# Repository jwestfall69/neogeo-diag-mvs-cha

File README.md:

# neogeo-diag-mvs-cha

## Overview
This is a custom NeoGeo MVS CHA board that is used in conjunction with the [NeoGeo Diag Bios](https://github.com/jwestfall69/neogeo-diag-bios) that allows for testing the Z80 sound system with a custom diag M1 rom.  This doesn't allow for any new type of testing that was done previously, but make it possible to create a diag CHA board without having to sacrifice a original SNK CHA board.

The NeoGeo uses bank switching to allow full access to the M1 rom.  This is normally handled by a custom NEO-ZMC chip on the CHA board.  I ended up making 3 different boards you can choose from to deal with this bank switching:

A Board that uses a original NEO-ZMC:
<br>

2 Boards that replace the NEO-ZMC with a CPLD (Socketed PLCC44 and TQFP44):

Personally I would go with the NEO-ZMC based board since the NEO-ZMC is available as NOS for around $2 each.  More on this in the BOM below.  Additionally with the chip shortage its a little difficult to get the CPLDs, plus the fun of programming them.

## PCB Manufacturing
PCB should be 1.6mm thickness.  With these boards likely being inserted and removed numerous times its suggested you use ENIG surface finishing and gold fingers w/chamfering.

I've been using [jlcpcb](https://jlcpcb.com/) for PCB manufacturing.  Just watch out that by default they will add an order number to the silk screen unless you tell them not to.

## BOMs
**IMPORTANT:**

  * The 32 pin DIP sockets listed in the BOMs are special low profile ones.  Normal sockets + EPROM are to tall for the board to be able to fit behind the PROG board.
  * Stock of the CPLD is pretty low everywhere.  If you can't find them on digikey/mouser, you might be able to buy them directly from [Microchip](https://www.microchipdirect.com/).
  * If you buy a used CPLD its possible the JTAG pins were repurposed as I/O pins.  This will make it impossible to re-program with JTAG.
  * When buying the EPROMs I would advise against buying any that claimed to be new.  Sellers claiming this maybe trying to sell 
  slower speed variants re-labeled as something faster or just straight up fakes.

### NEO-ZMC based board
| Quantity | Description | Part Number | Digikey | Notes |
|:--------:|:------------|-------------|---------|-------|
| 1        | NEO-ZMC | NEO-ZMC | | NOS Availible:<br> - On [Aliexpress](https://www.aliexpress.us/item/2251832763681253.html?gatewayAdapt=glo2usa4itemAdapt)<br>- On [arcade-projects.com](https://www.arcade-projects.com/threads/openkeys-neogeo-diag-prog-boards.24392/) |
| 2        | 74HC574 pin 14 SOIC | SN74HC574NSR | [296-31816-1-ND](https://www.digikey.com/en/products/detail/texas-instruments/SN74HC574NSR/1571235) | |
| 2       | Low Profile 32pin DIP Socket | 115-93-632-41-003000 | [ED5632-ND](https://www.digikey.com/en/products/detail/mill-max-manufacturing-corp/115-93-632-41-003000/81902) | This is optional if you want just solder the eproms to the board |
| 2       | 1Mbit (128k x 8bit) 32 pin EPROM, 150ns or faster | 27C1001<br>or<br>27C010 | | |
| 5        | 100nf / 0.1uf Ceramic Capacitor 0805 Size | CL21B104KBCNNNC | [1276-1003-2-ND](https://www.digikey.com/en/products/detail/samsung-electro-mechanics/CL21B104KBCNNNC/3886661) | Any 100nf 0805 is fine |

### CPLD PLCC44 (Socket) based board
| Quantity | Description | Part Number | Digikey | Notes |
|:--------:|:------------|-------------|---------|-------|
| 1        | CLPD PLCC 44 pin | Microchip/Atmel ATF1502AS-xxJU44<br>or<br>ATF1504AS-xxJU44 | [ATF1502AS-7JX44-ND](https://www.digikey.com/en/products/detail/microchip-technology/ATF1502AS-7JX44/1027048)<br>[ATF1504AS-10JU44](https://www.digikey.com/en/products/detail/microchip-technology/ATF1504AS-10JU44/1118923) | Other speeds should work too |
| 1        | PLCC 44 pin through hole socket | | | |
| 2        | 74HC574 pin 14 SOIC | SN74HC574NSR | [296-31816-1-ND](https://www.digikey.com/en/products/detail/texas-instruments/SN74HC574NSR/1571235) | |
| 2       | Low Profile 32pin DIP Socket | 115-93-632-41-003000 | [ED5632-ND](https://www.digikey.com/en/products/detail/mill-max-manufacturing-corp/115-93-632-41-003000/81902) | This is optional if you want just solder the eproms to the board |
| 2       | 1Mbit (128k x 8bit) 32 pin EPROM, 150ns or faster | 27C1001<br>or<br>27C010 | | |
| 8       | 100nf / 0.1uf Ceramic Capacitor 0805 Size | CL21B104KBCNNNC | [1276-1003-2-ND](https://www.digikey.com/en/products/detail/samsung-electro-mechanics/CL21B104KBCNNNC/3886661) | Any 100nf 0805 is fine |

### CPLD TQFP44 based board
| Quantity | Description | Part Number | Digikey | Notes |
|:--------:|:------------|-------------|---------|-------|
| 1        | CLPD TQFP 44 pin | Microchip/Atmel ATF1502AS-xxAU44<br>or<br>ATF1504AS-xxAU44 | [ATF1502AS-10AU44](https://www.digikey.com/en/products/detail/microchip-technology/ATF1502AS-10AU44/1008375)<br>[ATF1504AS-10AU44](https://www.digikey.com/en/products/detail/microchip-technology/ATF1504AS-10AU44/1008359) | Other speeds should work too |
| 2        | 74HC574 pin 14 SOIC | SN74HC574NSR | [296-31816-1-ND](https://www.digikey.com/en/products/detail/texas-instruments/SN74HC574NSR/1571235) | |
| 2       | Low Profile 32pin DIP Socket | 115-93-632-41-003000 | [ED5632-ND](https://www.digikey.com/en/products/detail/mill-max-manufacturing-corp/115-93-632-41-003000/81902) | This is optional if you want just solder the eproms to the board |
| 2       | 1Mbit (128k x 8bit) 32 pin EPROM, 150ns or faster | 27C1001<br>or<br>27C010 | | |
| 8       | 100nf / 0.1uf Ceramic Capacitor 0805 Size | CL21B104KBCNNNC | [1276-1003-2-ND](https://www.digikey.com/en/products/detail/samsung-electro-mechanics/CL21B104KBCNNNC/3886661) | Any 100nf 0805 is fine |

## Assembly
  * Reminder from above that normal 32 pin DIP sockets will be to tall
  * On the NEO-ZMC board, take note of pin 1 location of the NEO-ZMC chip as its rotated 180 degrees from what you might expect.

## Programming the CPLD

Both CPLD based boards have a JTAG port on left side that can be used for programming the CPLD.  I've been using this [FT232H](https://www.amazon.com/dp/B07T9CPMHT?psc=1&ref=ppx_yo2ov_dt_b_product_details) based programmer along with [openocd](https://openocd.org/) software to program the CPLD.

Here is a picture of the programmer and the cable I made for it:

The programmer has pin labels on the bottom of the board.

| Programmer PIN | J-TAG PIN |
|:--------------:|:---------:|
| AD0            | TCK       |
| AD1            | TDI       |
| AD2            | TDO       |
| AD3            | TMS       |
| GND            | GND       |
| +5V            | VCC       |

I haven't done JTAG stuff before, but believe this programmer not normal in that its supplying 5V to power the CPLD, whereas I think most JTAG programmers rely on something else to supply power to the CPLD and the VCC/GND pins are just used for VCC/GND reference.

Since this programmer is supplying power, it would be powering the entire CHA board including to the EPROMS/74HC574 chips.  I haven't run into any USB over current issues doing this.  Obviously don't plug in the programmer into the CHA board if its also plugged into an MVS motherboard.

Its not necessary to solder the JTAG cable to the JTAG port on the CHA board, just insert the pins into the through hole and hold it an angle so the pins are touching the sides of the through holes like this:

As noted above I've been using openocd software for programming.  I've only used it on linux and it should be an existing package your distro.  For the following openocd commands below the location of the um232h.cfg maybe different depending on where your distro installs interface config files.  Additionally if you use a different programmer you might need to use a completely different interface config.

**Make sure the CPLD is detected**
```
# openocd -f /usr/share/openocd/scripts/interface/ftdi/um232h.cfg -c "adapter speed 400" -c "transport select jtag" -c init -c scan_chain -c shutdown

Open On-Chip Debugger 0.11.0+dev-snapshot (2023-02-14-01:09)
Licensed under GNU GPL v2
For bug reports, read
        http://openocd.org/doc/doxygen/bugs.html
adapter speed: 400 kHz

jtag
Info : clock speed 400 kHz
Warn : There are no enabled taps.  AUTO PROBING MIGHT NOT WORK!!
Info : JTAG tap: auto0.tap tap/device found: 0x0150403f (mfg: 0x01f (Atmel), part: 0x1504, ver: 0x0)
Warn : AUTO auto0.tap - use "jtag newtap auto0 tap -irlen 3 -expected-id 0x0150403f"
Warn : gdb services need one or more targets defined
   TapName             Enabled  IdCode     Expected   IrLen IrCap IrMask
-- ------------------- -------- ---------- ---------- ----- ----- ------
 0 auto0.tap              Y     0x0150403f 0x00000000     3 0x01  0x03

shutdown command invoked

```
You want to see an IdCode of 0x01504xxx or 0x01502xxx based on which CPLD you are using.

**Programming the CPLD**<br>
For programming you will need the .svf firmware file for the CPLD you are using.  In the below example I have a ATF1504AS-7AX44 TQFP CPLD, so I use the atf1504as-tqfp44.svf firmware.

```
# openocd -f /usr/share/openocd/scripts/interface/ftdi/um232h.cfg -c "adapter speed 400" -c "transport select jtag" -c init -c "svf atf1504as-tqfp44/atf1504as-tqfp44.svf" -c shutdown

Open On-Chip Debugger 0.11.0+dev-snapshot (2023-02-14-01:09)
Licensed under GNU GPL v2
For bug reports, read
        http://openocd.org/doc/doxygen/bugs.html
adapter speed: 400 kHz

jtag
Info : clock speed 400 kHz
Warn : There are no enabled taps.  AUTO PROBING MIGHT NOT WORK!!
Info : JTAG tap: auto0.tap tap/device found: 0x0150403f (mfg: 0x01f (Atmel), part: 0x1504, ver: 0x0)
Warn : AUTO auto0.tap - use "jtag newtap auto0 tap -irlen 3 -expected-id 0x0150403f"
Warn : gdb services need one or more targets defined
svf processing file: "atf1504as-tqfp44/atf1504as-tqfp44.svf"
TRST ABSENT;
ENDIR IDLE;
ENDDR IDLE;
HDR 0;
HIR 0;
TDR 0;
TIR 0;
RUNTEST 50021E-6 SEC;
STATE RESET;
STATE IDLE;
RUNTEST 50021E-6 SEC;
SIR 10 TDI (280);
SDR 10 TDI (1b9);
STATE IDLE;
SIR 10 TDI (059);
        MASK (ffffffff);
STATE IDLE;
SIR 10 TDI (2b3);
SIR 10 TDI (29e);

...

SIR 10 TDI (293);
        MASK (ffff);
STATE IDLE;
SIR 10 TDI (2a1);
SDR 11 TDI (100);
SIR 10 TDI (28c);
STATE IDLE;
RUNTEST 20001E-6 SEC;
SIR 10 TDI (291);
        MASK (ffffffff);
STATE IDLE;
SIR 10 TDI (280);
SDR 10 TDI (000);
STATE IDLE;
RUNTEST 10001E-6 SEC;
STATE RESET;
RUNTEST 50021E-6 SEC;

Time used: 0m12s393ms
svf file programmed successfully for 3299 commands with 0 errors

shutdown command invoked

```

## Programming the EPROMs
The M1 EPROM should be programmed using the diag M1 ROM provided with the neogeo diag bios.

The S1 EPROM can be programmed with most any S1 ROM from any game.  I usually just use 201-s1.s1 from mslug mame romset.

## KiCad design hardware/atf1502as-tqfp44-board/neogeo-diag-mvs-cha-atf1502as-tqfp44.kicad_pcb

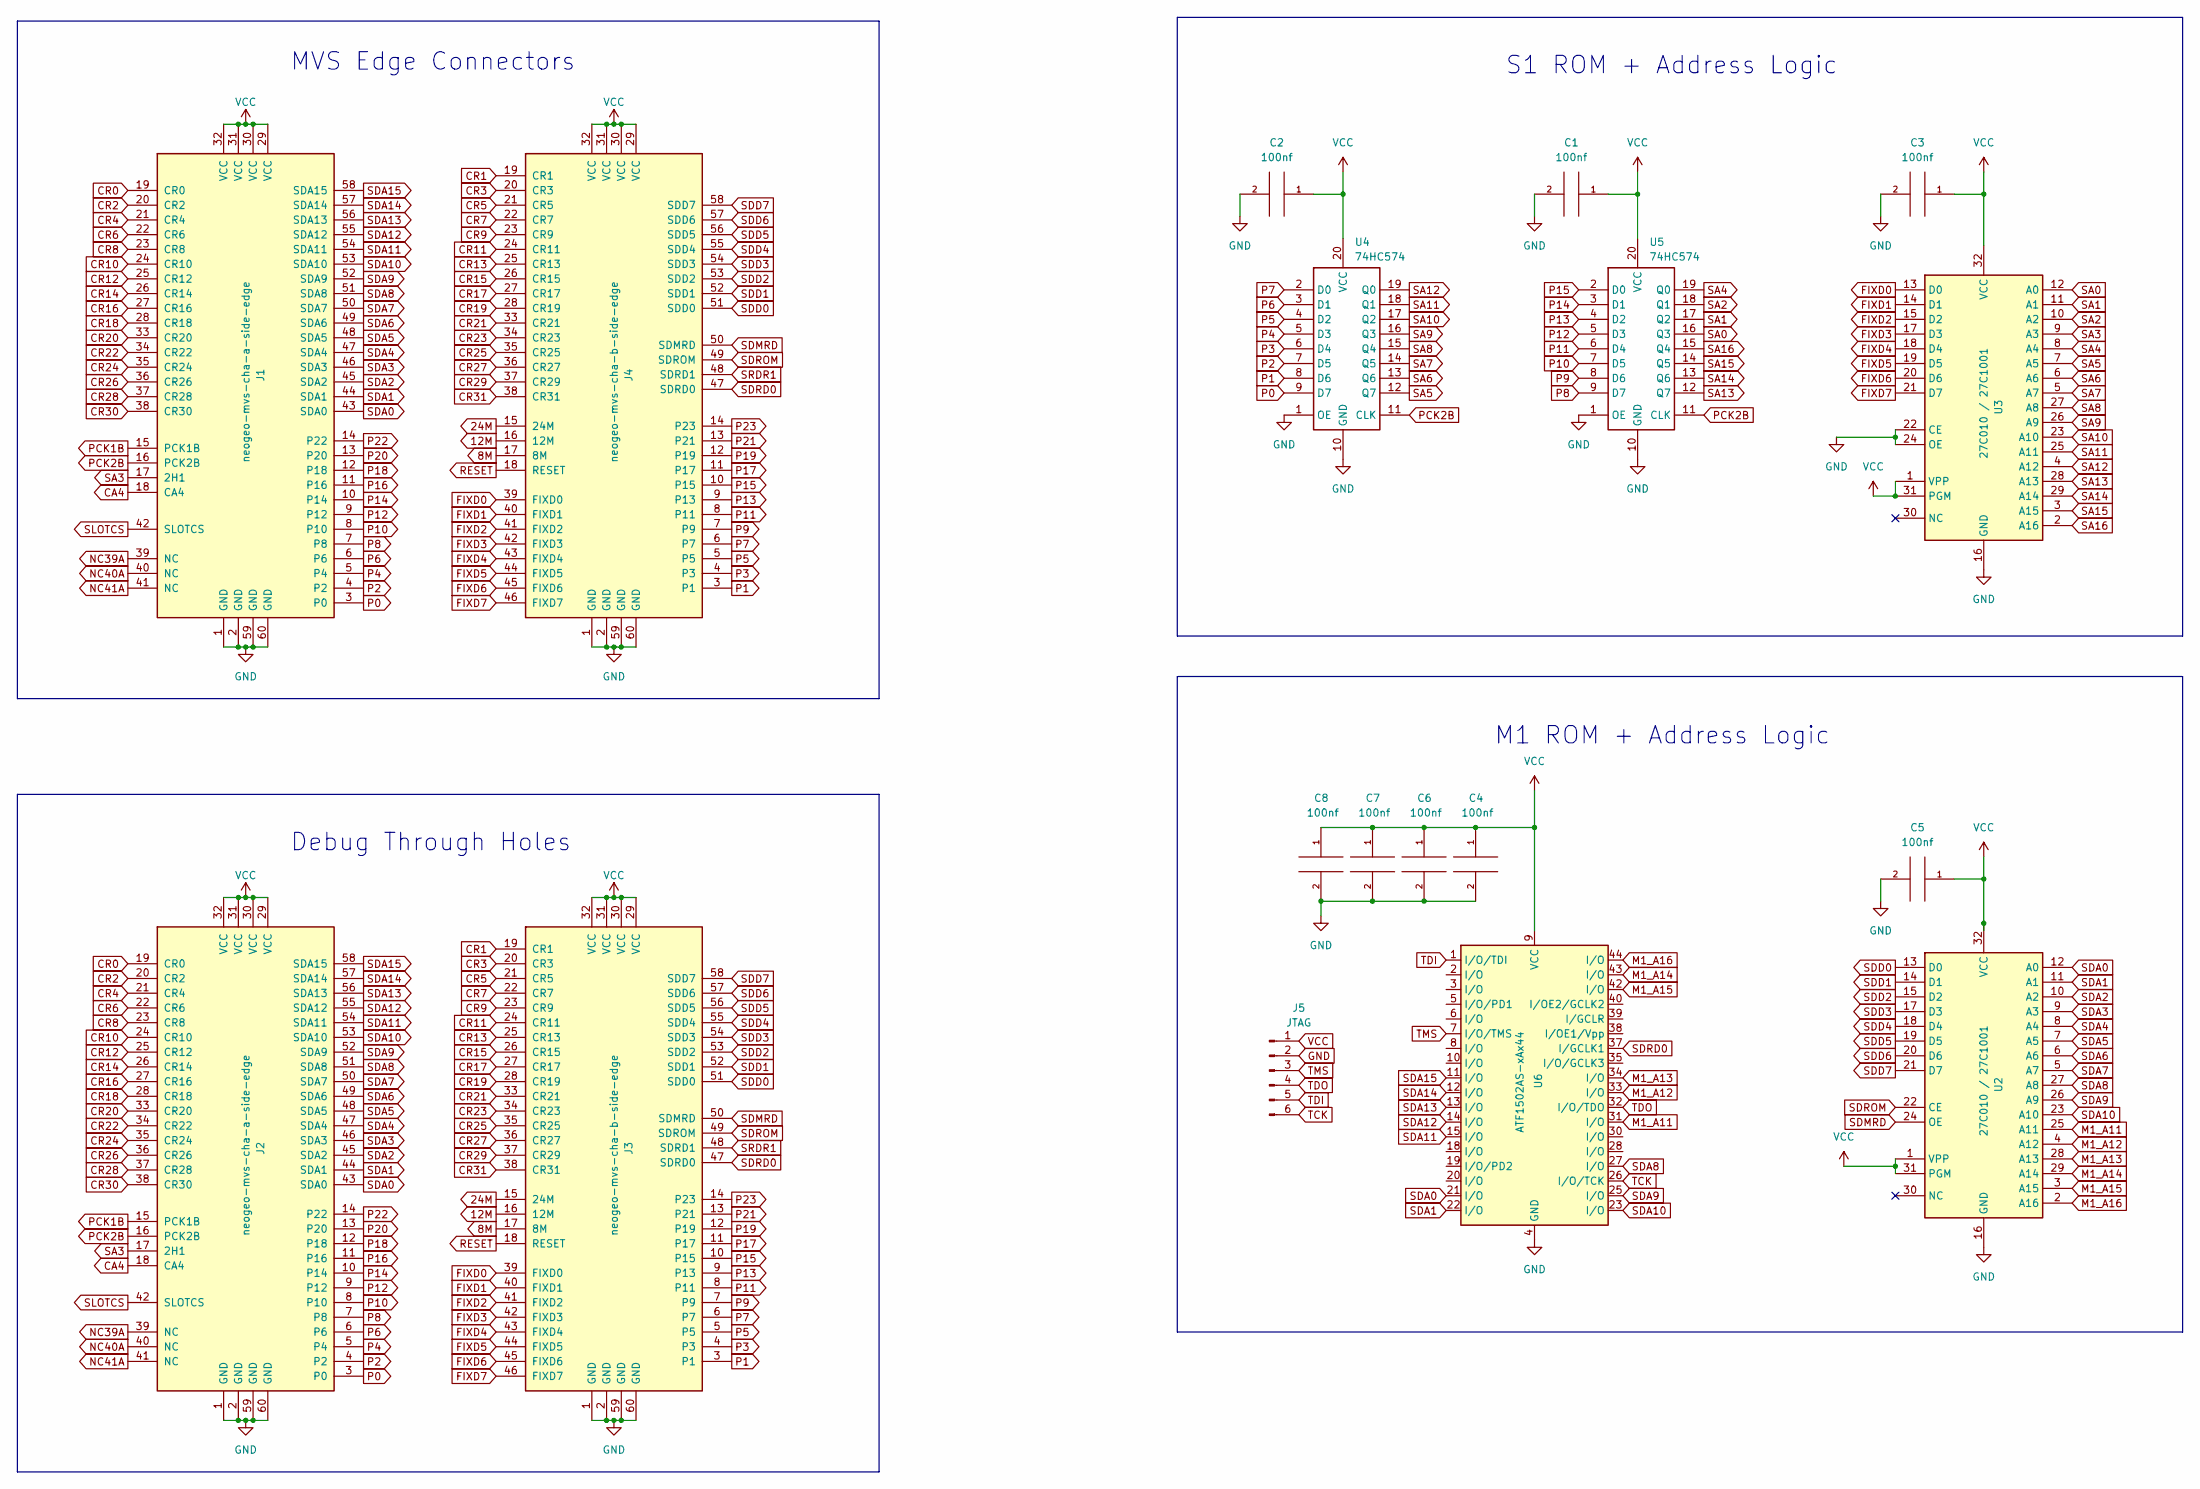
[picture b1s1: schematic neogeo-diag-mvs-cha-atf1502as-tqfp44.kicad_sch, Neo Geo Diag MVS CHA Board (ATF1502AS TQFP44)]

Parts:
C1, C2, C3, C4, C5, C6, C7, C8: 100nf; C_0805_2012Metric
J1: neogeo-mvs-cha-a-side-edge; neogeo-mvs-a-side-edge
J2: neogeo-mvs-cha-a-side-edge; neogeo-mvs-cha-edge-test-points
J3: neogeo-mvs-cha-b-side-edge; neogeo-mvs-cha-edge-test-points
J4: neogeo-mvs-cha-b-side-edge; neogeo-mvs-b-side-edge
J5: JTAG; PinHeader_1x06_P2.54mm_Vertical
U2, U3: 27C010 / 27C1001; DIP-32_W15.24mm_Socket_LongPads
U4, U5: 74HC574; SO-20_5.3x12.6mm_P1.27mm
U6: ATF1502AS-xAx44; TQFP-44_10x10mm_P0.8mm

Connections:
8M: J3.17 (8M), J4.17 (8M)
12M: J3.16 (12M), J4.16 (12M)
24M: J3.15 (24M), J4.15 (24M)
CA4: J1.18 (CA4), J2.18 (CA4)
CR0: J1.19 (CR0), J2.19 (CR0)
CR1: J3.19 (CR1), J4.19 (CR1)
CR2: J1.20 (CR2), J2.20 (CR2)
CR3: J3.20 (CR3), J4.20 (CR3)
CR4: J1.21 (CR4), J2.21 (CR4)
CR5: J3.21 (CR5), J4.21 (CR5)
CR6: J1.22 (CR6), J2.22 (CR6)
CR7: J3.22 (CR7), J4.22 (CR7)
CR8: J1.23 (CR8), J2.23 (CR8)
CR9: J3.23 (CR9), J4.23 (CR9)
CR10: J1.24 (CR10), J2.24 (CR10)
CR11: J3.24 (CR11), J4.24 (CR11)
CR12: J1.25 (CR12), J2.25 (CR12)
CR13: J3.25 (CR13), J4.25 (CR13)
CR14: J1.26 (CR14), J2.26 (CR14)
CR15: J3.26 (CR15), J4.26 (CR15)
CR16: J1.27 (CR16), J2.27 (CR16)
CR17: J3.27 (CR17), J4.27 (CR17)
CR18: J1.28 (CR18), J2.28 (CR18)
CR19: J3.28 (CR19), J4.28 (CR19)
CR20: J1.33 (CR20), J2.33 (CR20)
CR21: J3.33 (CR21), J4.33 (CR21)
CR22: J1.34 (CR22), J2.34 (CR22)
CR23: J3.34 (CR23), J4.34 (CR23)
CR24: J1.35 (CR24), J2.35 (CR24)
CR25: J3.35 (CR25), J4.35 (CR25)
CR26: J1.36 (CR26), J2.36 (CR26)
CR27: J3.36 (CR27), J4.36 (CR27)
CR28: J1.37 (CR28), J2.37 (CR28)
CR29: J3.37 (CR29), J4.37 (CR29)
CR30: J1.38 (CR30), J2.38 (CR30)
CR31: J3.38 (CR31), J4.38 (CR31)
FIXD0: J3.39 (FIXD0), J4.39 (FIXD0), U3.13 (D0)
FIXD1: J3.40 (FIXD1), J4.40 (FIXD1), U3.14 (D1)
FIXD2: J3.41 (FIXD2), J4.41 (FIXD2), U3.15 (D2)
FIXD3: J3.42 (FIXD3), J4.42 (FIXD3), U3.17 (D3)
FIXD4: J3.43 (FIXD4), J4.43 (FIXD4), U3.18 (D4)
FIXD5: J3.44 (FIXD5), J4.44 (FIXD5), U3.19 (D5)
FIXD6: J3.45 (FIXD6), J4.45 (FIXD6), U3.20 (D6)
FIXD7: J3.46 (FIXD7), J4.46 (FIXD7), U3.21 (D7)
GND: C1.2, C2.2, C3.2, C4.2, C5.2, C6.2, C7.2, C8.2, J1.1 (GND), J1.2 (GND), J1.59 (GND), J1.60 (GND), J2.1 (GND), J2.2 (GND), J2.59 (GND), J2.60 (GND), J3.1 (GND), J3.2 (GND), J3.59 (GND), J3.60 (GND), J4.1 (GND), J4.2 (GND), J4.59 (GND), J4.60 (GND), J5.2, U2.16 (GND), U3.16 (GND), U3.22 (CE), U3.24 (OE), U4.1 (OE), U4.10 (GND), U5.1 (OE), U5.10 (GND), U6.4 (GND), U6.16 (GND), U6.24 (GND), U6.36 (GND)
M1_A11: U2.25 (A11), U6.31 (I/O)
M1_A12: U2.4 (A12), U6.33 (I/O)
M1_A13: U2.28 (A13), U6.34 (I/O)
M1_A14: U2.29 (A14), U6.43 (I/O)
M1_A15: U2.3 (A15), U6.42 (I/O)
M1_A16: U2.2 (A16), U6.44 (I/O)
NC39A: J1.39 (NC), J2.39 (NC)
NC40A: J1.40 (NC), J2.40 (NC)
NC41A: J1.41 (NC), J2.41 (NC)
P0: J1.3 (P0), J2.3 (P0), U4.9 (D7)
P1: J3.3 (P1), J4.3 (P1), U4.8 (D6)
P2: J1.4 (P2), J2.4 (P2), U4.7 (D5)
P3: J3.4 (P3), J4.4 (P3), U4.6 (D4)
P4: J1.5 (P4), J2.5 (P4), U4.5 (D3)
P5: J3.5, J4.5, U4.4 (D2)
P6: J1.6, J2.6, U4.3 (D1)
P7: J3.6 (P7), J4.6 (P7), U4.2 (D0)
P8: J1.7 (P8), J2.7 (P8), U5.9 (D7)
P9: J3.7 (P9), J4.7 (P9), U5.8 (D6)
P10: J1.8 (P10), J2.8 (P10), U5.7 (D5)
P11: J3.8 (P11), J4.8 (P11), U5.6 (D4)
P12: J1.9 (P12), J2.9 (P12), U5.5 (D3)
P13: J3.9 (P13), J4.9 (P13), U5.4 (D2)
P14: J1.10 (P14), J2.10 (P14), U5.3 (D1)
P15: J3.10 (P15), J4.10 (P15), U5.2 (D0)
P16: J1.11 (P16), J2.11 (P16)
P17: J3.11 (P17), J4.11 (P17)
P18: J1.12 (P18), J2.12 (P18)
P19: J3.12 (P19), J4.12 (P19)
P20: J1.13 (P20), J2.13 (P20)
P21: J3.13 (P21), J4.13 (P21)
P22: J1.14 (P22), J2.14 (P22)
P23: J3.14 (P23), J4.14 (P23)
PCK1B: J1.15 (PCK1B), J2.15 (PCK1B)
PCK2B: J1.16 (PCK2B), J2.16 (PCK2B), U4.11 (CLK), U5.11 (CLK)
RESET: J3.18 (RESET), J4.18 (RESET)
SA0: U3.12 (A0), U5.16 (Q3)
SA1: U3.11 (A1), U5.17 (Q2)
SA2: U3.10 (A2), U5.18 (Q1)
SA3: J1.17 (2H1), J2.17 (2H1), U3.9 (A3)
SA4: U3.8 (A4), U5.19 (Q0)
SA5: U3.7 (A5), U4.12 (Q7)
SA6: U3.6 (A6), U4.13 (Q6)
SA7: U3.5 (A7), U4.14 (Q5)
SA8: U3.27 (A8), U4.15 (Q4)
SA9: U3.26 (A9), U4.16 (Q3)
SA10: U3.23 (A10), U4.17 (Q2)
SA11: U3.25 (A11), U4.18 (Q1)
SA12: U3.4 (A12), U4.19 (Q0)
SA13: U3.28 (A13), U5.12 (Q7)
SA14: U3.29 (A14), U5.13 (Q6)
SA15: U3.3 (A15), U5.14 (Q5)
SA16: U3.2 (A16), U5.15 (Q4)
SDA0: J1.43 (SDA0), J2.43 (SDA0), U2.12 (A0), U6.21 (I/O)
SDA1: J1.44 (SDA1), J2.44 (SDA1), U2.11 (A1), U6.22 (I/O)
SDA2: J1.45 (SDA2), J2.45 (SDA2), U2.10 (A2)
SDA3: J1.46 (SDA3), J2.46 (SDA3), U2.9 (A3)
SDA4: J1.47 (SDA4), J2.47 (SDA4), U2.8 (A4)
SDA5: J1.48 (SDA5), J2.48 (SDA5), U2.7 (A5)
SDA6: J1.49 (SDA6), J2.49 (SDA6), U2.6 (A6)
SDA7: J1.50 (SDA7), J2.50 (SDA7), U2.5 (A7)
SDA8: J1.51 (SDA8), J2.51 (SDA8), U2.27 (A8), U6.27 (I/O)
SDA9: J1.52 (SDA9), J2.52 (SDA9), U2.26 (A9), U6.25 (I/O)
SDA10: J1.53 (SDA10), J2.53 (SDA10), U2.23 (A10), U6.23 (I/O)
SDA11: J1.54 (SDA11), J2.54 (SDA11), U6.15 (I/O)
SDA12: J1.55 (SDA12), J2.55 (SDA12), U6.14 (I/O)
SDA13: J1.56 (SDA13), J2.56 (SDA13), U6.13 (I/O)
SDA14: J1.57 (SDA14), J2.57 (SDA14), U6.12 (I/O)
SDA15: J1.58 (SDA15), J2.58 (SDA15), U6.11 (I/O)
SDD0: J3.51 (SDD0), J4.51 (SDD0), U2.13 (D0)
SDD1: J3.52 (SDD1), J4.52 (SDD1), U2.14 (D1)
SDD2: J3.53 (SDD2), J4.53 (SDD2), U2.15 (D2)
SDD3: J3.54 (SDD3), J4.54 (SDD3), U2.17 (D3)
SDD4: J3.55 (SDD4), J4.55 (SDD4), U2.18 (D4)
SDD5: J3.56 (SDD5), J4.56 (SDD5), U2.19 (D5)
SDD6: J3.57 (SDD6), J4.57 (SDD6), U2.20 (D6)
SDD7: J3.58 (SDD7), J4.58 (SDD7), U2.21 (D7)
SDMRD: J3.50 (SDMRD), J4.50 (SDMRD), U2.24 (OE)
SDRD0: J3.47 (SDRD0), J4.47 (SDRD0), U6.37 (I/GCLK1)
SDROM: J3.49 (SDROM), J4.49 (SDROM), U2.22 (CE)
SLOTCS: J1.42 (SLOTCS), J2.42 (SLOTCS)
SRDR1: J3.48 (SDRD1), J4.48 (SDRD1)
TCK: J5.6, U6.26 (I/O/TCK)
TDI: J5.5, U6.1 (I/O/TDI)
TDO: J5.4, U6.32 (I/O/TDO)
TMS: J5.3, U6.7 (I/O/TMS)
VCC: C1.1, C2.1, C3.1, C4.1, C5.1, C6.1, C7.1, C8.1, J1.29 (VCC), J1.30 (VCC), J1.31 (VCC), J1.32 (VCC), J2.29 (VCC), J2.30 (VCC), J2.31 (VCC), J2.32 (VCC), J3.29 (VCC), J3.30 (VCC), J3.31 (VCC), J3.32 (VCC), J4.29 (VCC), J4.30 (VCC), J4.31 (VCC), J4.32 (VCC), J5.1, U2.1 (VPP), U2.31 (PGM), U2.32 (VCC), U3.1 (VPP), U3.31 (PGM), U3.32 (VCC), U4.20 (VCC), U5.20 (VCC), U6.9 (VCC), U6.17 (VCC), U6.29 (VCC), U6.41 (VCC)

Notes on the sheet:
Debug Through Holes
MVS Edge Connectors
S1 ROM + Address Logic
M1 ROM + Address Logic

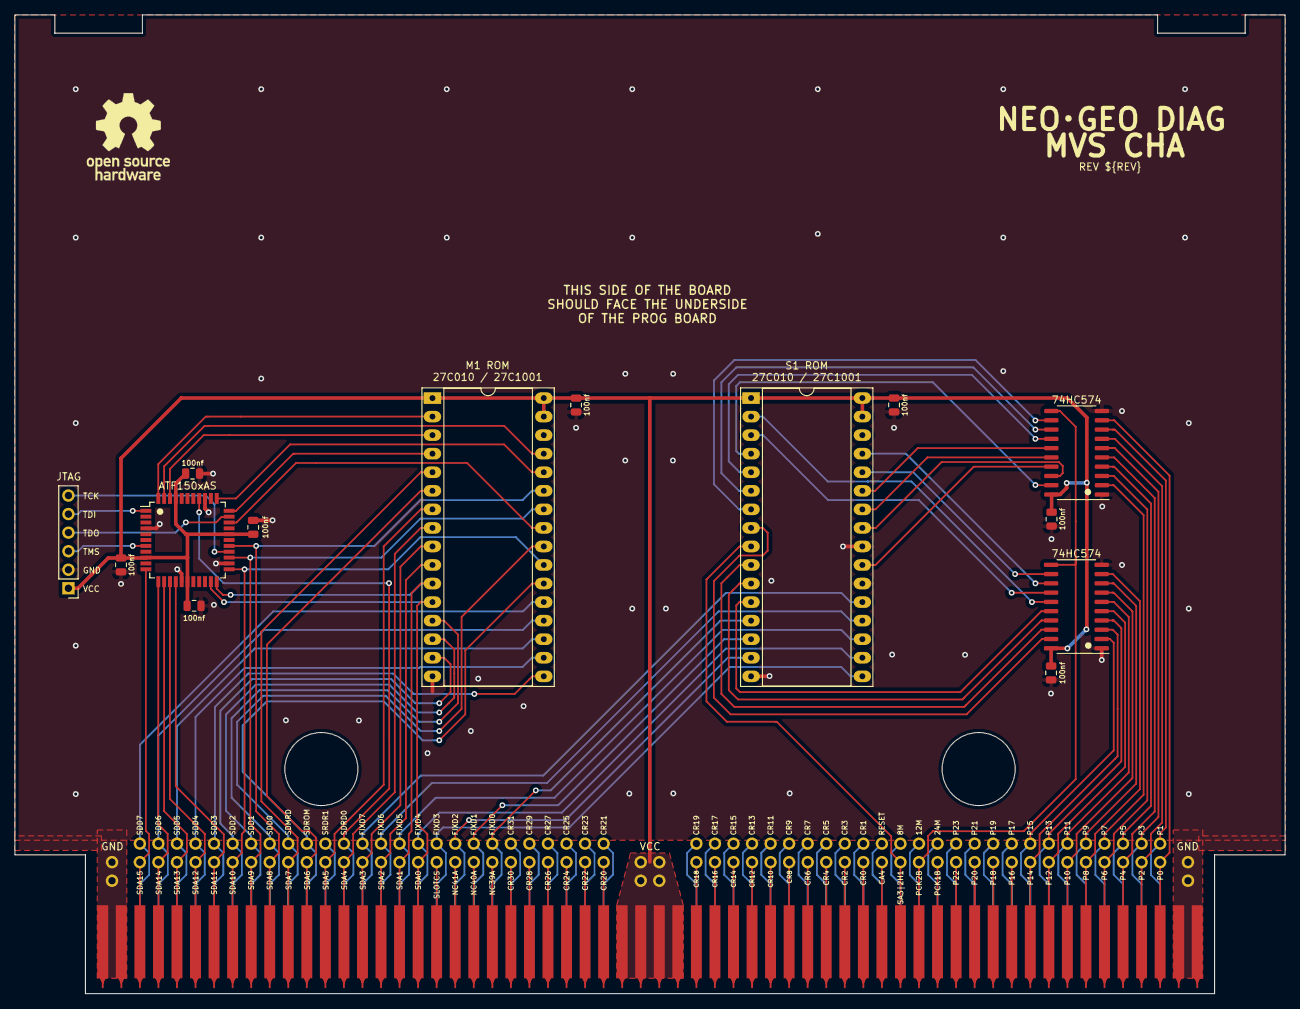
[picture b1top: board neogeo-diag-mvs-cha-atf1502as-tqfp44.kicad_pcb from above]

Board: 2 copper layers, 173.9 x 134.0 mm, 18 parts (1 on the bottom side), 132 nets.

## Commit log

2023-08-09 Project Skeleton
2023-08-09 Add neo-zmc based board
2023-08-09 Add atf1502as plcc44 board
2023-08-09 Add atf1502as tqfp44 board
2023-08-10 Add CPLD firmware
2023-08-11 Add images of boards and programmer w/cable
2023-08-12 Ignore .lck files and remove the one that was accidentally added
2023-08-12 Start of docs
2023-08-13 Some minor tweaks to schematics and pcbs
2023-08-13 Bump revision number on all boards so they are the same
